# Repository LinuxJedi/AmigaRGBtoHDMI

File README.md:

# AmigaRGBtoHDMI

LinuxJedi's designs for Amiga RGBtoHDMI boards.

**ATTENTION PI Zero 2W users**: You can now use a Pi Zero 2W with the CPLD RGBtoHDMI using the December 24th 2021 release.

## Amiga RGBtoHDMI Tester

If you are a builder of these boards I have designed a tester that safely tests these boards without requiring a Denise or Amiga. This reduces any potential damage and test if you don't have a specific Amiga model. These can be found [on Tindie](https://www.tindie.com/products/linuxjedi/amiga-rgbtohdmi-tester/).

## Choosing a CPLD

I am deliberately vague in which CPLD can be used in the boards here because many variants will work. Given chip shortages in recent years, you might want to pick any chip you can obtain rather than what is normally cheapest. I'll give a breakdown of what the model numbers look like and what to look out for. As an example I'll use `XC9572XL-10VQG44C`:

* `XC9572XL` - This part of the model number is required. Defines the type of logic chip and the number of logic cells. This is what you should search for from your supplier and then use the below to pick the right chip for you.
* `10` - is the maximum speed grade in ns. 10 is the slowest (cheapest) you can buy. The max speed this board will go is 35ns, so 10ns is plenty.
* `VQ` - means it is a QFP. You could modify the board to accept the PLCC variant, but that would require you to make some changes in KiCad. The firmware is compatible with both.
* `G` - means lead-free / RoHS compliant. Without the `G` means the legs have lead.
* `44` - number of pins. You could in-theory modify the board for more pins in KiCad. This would require a firmware change too, which in-turn means modifying the firmware loader, so I don't recommend it.
* `C` - Consumer grade (cheapest), if there is an `I` here that means "Industrial grade" (more expensive) and `A` means "Automotive grade" (crazy expensive). This mostly defines the max/min temperature the chip will work at.

My recommendation if you can obtain it, is the XC9572XL-10VQG44C (or without the `G`). But the only important parts are the `XC9572XL`, the `VQ` and the `44`.

## Projects in This Tree

### Amiga500CPLD

Amiga 500 CPLD variant that does not require a jumper and has no sparkling pixel issues.

### Amiga2000CPLDSlot

Amiga 2000 CPLD variant that does not require a jumper and has no sparkling pixel issues

### Amiga1000CPLD

Amiga 1000 CPLD variant that does not require a jumper and has no sparkling pixel issues

### Legacy boards

The legacy boards directory contains:

* Amiga 2000 RGBtoHDMI v2
* Amiga 2000 CPLD RGBtoHDMI v1.2
* Amiga 2000 CPLD RGBtoHDMI v2.1

These have been superseeded by the Amiga 2000 CPLD RGBtoHDMI v2.2 board.

* Amiga 500 CPLD v1

This has been superseeded by the Amiga 500 CPLD RGBtoHDMI v2.0 board.

## Other versions

- c0pperdragon's - The excellent original c0pperdragon design can be found at: https://github.com/c0pperdragon/Amiga-Digital-Video/
- solarmon's - Improved versions of c0pperdragon's design to relocate the Pi and add additional features:https://github.com/solarmon/RGBtoHDMI

Please add pull requests to link to your variants here.

## Software

The software used for this project can be found at https://github.com/hoglet67/RGBtoHDMI/

## Troubleshooting

### Cannot use the CPLD flash menu

By default the RGBtoHDMI software is in three button mode. You need to copy the profiles in the instructions for your board which sets up a few things including the single button mode.

## Ready Built Boards

If you want a ready built board for either design please contact andrew@linuxjedi.co.uk and I can put you in touch with whoever is building / selling at a reasonable price.

Likewise if you are a someone selling these designs, please let me know if you want me to put you in touch with buyers who contact me.

I also sell some of these designs [on Tindie](https://www.tindie.com/stores/linuxjedi/).

Alternatively I've made the PCBs available on PCBWay here: https://www.pcbway.com/project/member/?bmbno=0369642B-E3DA-48

## Sponsorship

If you like these projects and have built / sold a few yourself, please consider sponsoring. R&D for these projects isn't cheap and the sponsorship money goes into more designs for the future. Links for this are can be found in the "Sponsor" button at the top of the GitHub page for this project.

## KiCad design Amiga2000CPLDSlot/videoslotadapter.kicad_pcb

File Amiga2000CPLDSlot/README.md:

# Amiga CPLD Video Slot Adapter

This adaptor uses a CPLD to pass the RGB and sync signals from the Amiga 2000 video slot to the Rasperry Pi Zero. It derives the pixel clock in a very different way to other designs and therefore does not require a jumper for Denise / Super Denise and has no "sparkling" pixel issues. It also has the advantage of being firmware upgradable if there are any issues found in the logic.

Version 2 of this board is logically identical to version 1, but is designed to be easier to build and easier for the user to install. The Pi faces the rear of the Amiga so that the HDMI can be plugged directly into it and instead of wires it uses physical buttons.

Version 2.2 has been changed to make the board smaller. It includes a fuse due to a few users misaligning the Pi, causing a sort between +5v and GND which in-turn caused the +5v line to burn. It also includes an optional LED to indicate there is power to the +5v line (that the fuse hasn't blown).

**ATTENTION PI Zero 2W users**: You can now use a Pi Zero 2W with the CPLD RGBtoHDMI using 24th December 2021 release onwards.

## BOM

| Symbol       | Component                                    |
| ------------ | -------------------------------------------- |
| C1 - C3      | 0.1uF 0603                                   |
| J1           | 2x20pin socket 2.54mm                        |
| SW1 - SW3    | SKHHLQA010 90° SPST 8.35mm push button       |
| R1           | 1K 0603                                      |
| R3           | 4.7K 0603                                    |
| U1           | XC9572XL 44pin QFP                           |
| F1           | Littlefuse 1206L075THYR                      |
| D1           | Any 0603 LED                                 |
| R2           | A 0603 resistor between the LED and +5v line |

### Notes

- R1 needs to be a 1K pull resistor due to the low value internal I2C pull resisors in the Pi. If the value is too high then the software won't detect this is an Amiga board and won't show the correct firmware in the recovery menu.
- The F1 fuse can be any 1206 fuse with a hold current of 0.75A or greater. You could also just use a 0ohm resistor if you do not wish to use a fuse.
- D1 and R2 are optional, used as indication that the 5V line is being provided to the Pi and there is no fuse trip.
- This board can be used in single button mode with just SW1.
- You can use smaller push buttons but they won't reach outside of the A2000's case, this may be fine with the correct bracket.
- Brackets for the original A2000 RGBtoHDMI boards are **NOT** compatible, the mounting holes have been moved.
- It is recommended you use 4x11mm M2.5 standoffs to hold the Pi in place, alternatively you can use 10mm M2.5 standoffs and 1mm M2.5 washers.
- The board was designed in a KiCad 6.99 nightly build, you will need to use 6.99 (or higher if you are reading this after 7.0 is released) to be able to use the files.

## Pi Software Installation

The software on the Pi should be at least the latest 20211224 release from the [main tree](https://github.com/hoglet67/RGBtoHDMI/releases) or the latest [IanSB beta release](https://github.com/IanSB/RGBtoHDMI/releases) extracted onto a micro SD card in FAT32 format.

You need to copy some canned profile files into place for the board:

* `Amiga_CPLD_Readme/Amiga_2000_CPLD_Setup/profile_6-12_BIT_RGB.txt` to the root of the SD card
* `Amiga_CPLD_Readme/Amiga_2000_CPLD_Setup/Profiles/Default.txt` to the `Profiles` directory

This resolves some issues with mode switching, particularly on NTSC machines.

If you wish to use three button mode, you then need to edit `Profiles/Default.txt` and set the option `single_button_mode=0` (it is near the bottom of the file).

## Flashing the CPLD

The CPLD will need flashing with the `6-12_BIT_RGB_CPLD` firmware. The other firmware options are not compatible with this board.

If you have followed the software steps above you will get a recovery menu, select `6-12_BIT_RGB_CPLD`, confirm and the Pi will flash the CPLD and reboot.

## Initial Setup

You may see a shimmer or wavy effect. This is because the phase is set incorrectly and needs calibration, this is a one-off easy thing to do. If you have a static image such as the Kickstart 1.3 boot screen or Workbench with no mouse movement you can use the "Auto Calibrate Video Settings" option (it will require you to select twice to activate). Alternatively you can go into the "Sampling" menu and change the "Sampling Phase" until the image looks correct. Typically 0, 3 or 5 will work fine, but it could be different in each machine.

Once calibrated choose "Save Configuration" and this will be remembered for subsequent boots.

## Buying PCBs

You can buy PCBs from my store, [Retro Supplies](https://www.retrosupplies.co.uk/amiga-rgbtohdmi/rgbtohdmi-for-amiga-2000-v22-pcb-only).

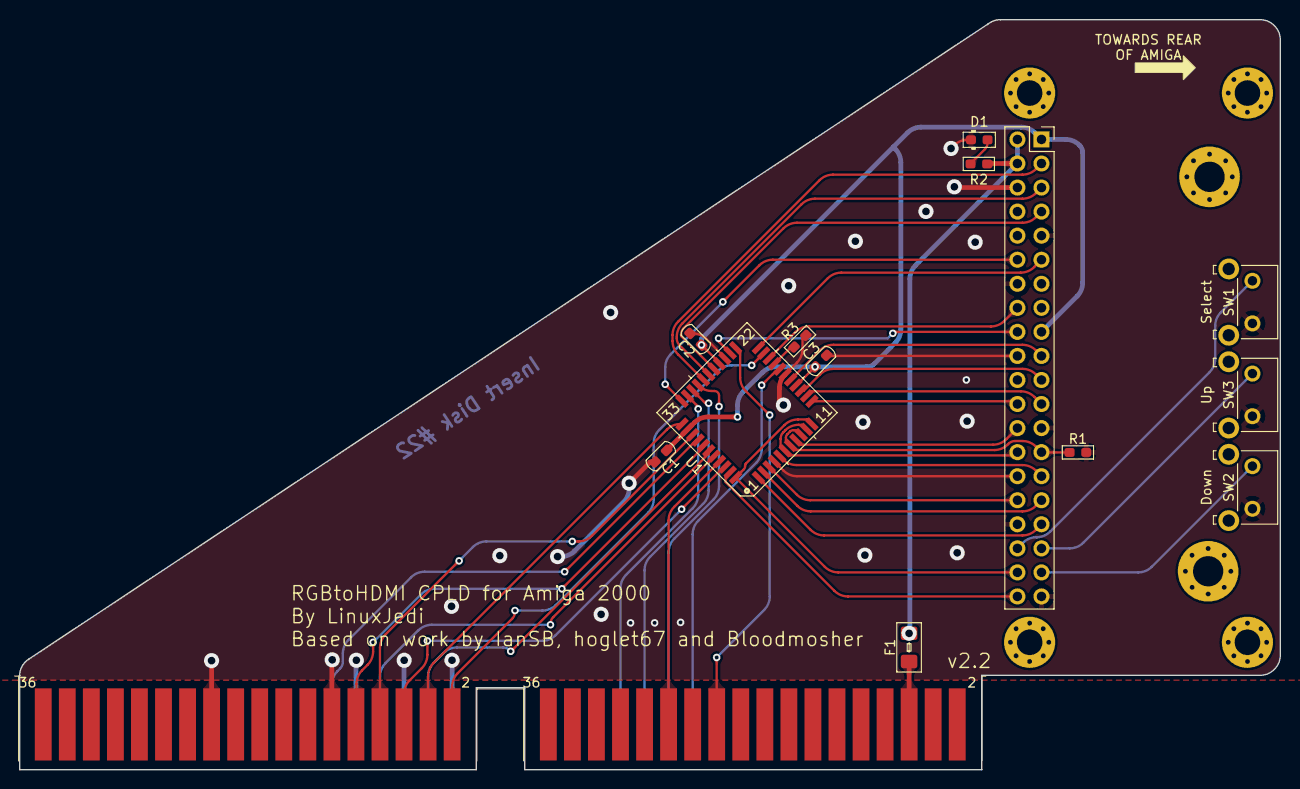
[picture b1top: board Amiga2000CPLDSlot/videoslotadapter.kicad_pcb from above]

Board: 2 copper layers, 133.1 x 79.2 mm, 20 parts (0 on the bottom side), 43 nets.

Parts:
C1, C2, C3: 0.1uF; C_0603_1608Metric_Pad1.08x0.95mm
D1: LED; D_0603_1608Metric_Pad1.05x0.95mm
F1: 500mA; Fuse_1206_3216Metric_Pad1.42x1.75mm_BigPads
H1, H2, H3, H4: MountingHole; MountingHole_2.7mm_M2.5_Pad_Via
H5, H6: MountingHole; MountingHole_3.2mm_M3_Pad_Via
J1: Raspberry_Pi_2_3; PinSocket_2x20_P2.54mm_Vertical
JVideoSlot1: A2000_Video_Slot_Phys; A2000_Video_Slot
R1: 1K; R_0603_1608Metric_Pad1.05x0.95mm_HandSolder
R2: R; R_0603_1608Metric_Pad1.05x0.95mm_HandSolder
R3: 4.7K; R_0603_1608Metric_Pad1.05x0.95mm_HandSolder
SW1: Select; SW_Tactile_SKHH_Angled
SW2: Down; SW_Tactile_SKHH_Angled
SW3: Up; SW_Tactile_SKHH_Angled
U1: XC9572VQ44; TQFP-44_10x10mm_P0.8mm

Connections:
+3V3: C1.1, C2.1, C3.1, J1.1 (3V3), J1.17 (3V3), U1.15 (VCC), U1.26 (VCCIO), U1.35 (VCC)
+5V: F1.2, J1.2 (5V), J1.4 (5V), R2.2
/B0: JVideoSlot1.23 (BO=DI(47-Ohm)), U1.18 (FB3M16)
/B1: JVideoSlot1.46 (B1), U1.38 (FB2M17)
/B2: JVideoSlot1.47 (B2), U1.37 (FB2M15)
/B3: JVideoSlot1.25 (B3=DB(47-Ohm)), U1.30 (FB2M5)
/CLKEN: J1.28 (ID_SC/GPIO1), U1.6 (FB3M5), U1.10 (TMS)
/DETECT: R3.1, U1.19 (FB4M2)
/G0: JVideoSlot1.42 (G0), U1.42 (FB1M8)
/G1: JVideoSlot1.43 (G1), U1.40 (FB1M5)
/G2: JVideoSlot1.44 (G2), U1.36 (I/O/GTS1)
/G3: JVideoSlot1.27 (G3=DG(47-Ohm)), U1.31 (FB2M6)
/GPIO0: J1.27 (ID_SD/GPIO0), R1.1, U1.7 (FB3M8), U1.9 (TDI)
/GPIO2: J1.3 (SDA/GPIO2), U1.29 (FB2M2)
/GPIO3: J1.5 (SCL/GPIO3), U1.28 (FB4M17)
/GPIO4: J1.7 (GCLK0/GPIO4), U1.27 (FB4M15)
/GPIO5: J1.29 (GCLK1/GPIO5), U1.5 (FB3M2)
/GPIO6: J1.31 (GCLK2/GPIO6), U1.2 (FB1M15)
/GPIO7: J1.26 (~CE1/GPIO7), U1.8 (FB3M9)
/GPIO8: J1.24 (~CE0/GPIO8), U1.12 (FB3M11)
/GPIO9: J1.21 (MISO0/GPIO9), U1.14 (FB3M15)
/GPIO10: J1.19 (MOSI0/GPIO10), U1.16 (FB3M17)
/GPIO11: J1.23 (SCLK0/GPIO11), U1.13 (FB3M14)
/GPIO12: J1.32 (PWM0/GPIO12), U1.3 (FB1M17)
/GPIO13: J1.33 (PWM1/GPIO13), U1.1 (I/O/GCK3)
/GPIO16: J1.36 (GPIO16), SW1.1
/GPIO17: J1.11 (GPIO17), U1.22 (FB4M11)
/GPIO18: J1.12 (GPIO18/PWM0), U1.33 (I/O/GSR)
/GPIO19: J1.35 (GPIO19/MISO1), SW3.1
/GPIO20: J1.38 (GPIO20/MOSI1), U1.11 (TCK), U1.44 (I/O/GCK2)
/GPIO21: J1.40 (GPIO21/SCLK1), U1.43 (I/O/GCK1)
/GPIO23: J1.16 (GPIO23), U1.20 (FB4M5)
/GPIO24: J1.18 (GPIO24), U1.24 (TDO)
/GPIO26: J1.37 (GPIO26), SW2.1
/HSYNC: JVideoSlot1.22 (/HSYNC(47-Ohm)), U1.23 (FB4M14)
/R0: JVideoSlot1.38 (R0), U1.21 (FB4M8)
/R1: JVideoSlot1.39 (R1), U1.39 (FB1M2)
/R2: JVideoSlot1.40 (R2), U1.34 (I/O/GTS2)
/R3: JVideoSlot1.29 (R3=DR(47-Ohm)), U1.32 (FB2M8)
/VSYNC: JVideoSlot1.26 (/VSYNC(47-Ohm)), U1.41 (FB1M6)
GND: C1.2, C2.2, C3.2, D1.1 (K), J1.6 (GND), J1.9 (GND), J1.14 (GND), J1.20 (GND), J1.25 (GND), J1.30 (GND), J1.34 (GND), J1.39 (GND), JVideoSlot1.37 (Ground), JVideoSlot1.41 (Ground), JVideoSlot1.45 (Ground), JVideoSlot1.48 (Ground), JVideoSlot1.58 (Ground), R1.2, R3.2, SW1.2, SW2.2, SW3.2, U1.4 (GND), U1.17 (GND), U1.25 (GND)
unnamed: D1.2 (A), R2.1
VCC: F1.1, JVideoSlot1.6 (+5_VDC_(2A))

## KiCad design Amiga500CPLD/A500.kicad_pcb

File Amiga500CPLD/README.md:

# Amiga 500 CPLD RGBtoHDMI

This adaptor uses a CPLD to pass the RGB and sync signals from the Amiga 500 Denise socket to the Rasperry Pi Zero. It derives the pixel clock in a very different way to the c0pperdragon design and therefore does not require a jumper for Denise / Super Denise and has no "sparkling" pixel issues. It also has the advantage of being firmware upgradable if there are any issues found in the logic.

**ATTENTION PI Zero 2W users**: You can now use a Pi Zero 2W with the CPLD RGBtoHDMI using the December 24th 2021 release.

## BOM

| Symbol     | Component                         |
| ---------- | --------------------------------- |
| C1 - C3    | 0.1uF 0603                        |
| J1         | 2x20pin socket 2.54mm             |
| JP1        | 2pin right angle header 2.54mm    |
| J2         | 1pin right angle header 2.54mm    |
| R1         | 1K 0603                           |
| R2         | 4.7K 0603                         |
| U1         | 48pin DIP socket 2.54mm           |
| U2         | 2x24pin SILs machined pins 2.54mm |
| U3         | XC9572XL 44pin QFP                |

### Notes

- It is important that R1 is 1K due to the low value of the internal pull resistor in GPIO0 of the Pi, the other pull resistors are more flexible (R1 is optional as the Pi will pull this internally). If the value is too high then the software won't detect this is an Amiga board and won't show the correct firmware in the recovery menu.
- You'll need some kind of push button to connect to JP1
- J2 is optional, it is only needed for revision 3 motherboards to clip onto pin 9 of U41 on the Amiga (photo coming soon)
- The Pi mounting holes are M2.5, 11mm posts or 10mm with 1mm washers are recommended

## Pi Software Installation

The software on the Pi should be at least the latest 20210529 release from the [main tree](https://github.com/hoglet67/RGBtoHDMI/releases) or the latest [IanSB beta release](https://github.com/IanSB/RGBtoHDMI/releases) extracted onto a micro SD card in FAT32 format.

You need to copy some canned profile files into place for the board:

* `Amiga_CPLD_Readme/Amiga_CPLD_Setup/profile_6-12_BIT_RGB.txt` to the root of the SD card
* `Amiga_CPLD_Readme/Amiga_CPLD_Setup/Profiles/Default.txt` to the `Profiles` directory

This resolves some issues with mode switching, particularly on NTSC machines. The profile copied will automatically set `single_button_mode`.

## Flashing the CPLD

The CPLD will need flashing with the `6-12_BIT_RGB_CPLD` firmware. The other firmware options are not compatible with the profiles.

If you have followed the software steps above you will get a recovery menu, select `6-12_BIT_RGB_CPLD`, confirm and the Pi will flash the CPLD and reboot. You can then jump to the Initial Setup section below.

## Initial Setup

You may also a shimmer or wavy effect. This is because the phase is set incorrectly and needs calibration, this is a one-off easy thing to do. If you have a static image such as the Kickstart 1.3 boot screen or Workbench with no mouse movement you can use the "Auto Calibrate Video Settings" option (it will require you to select twice to activate). Alternatively you can go into the "Sampling" menu and change the "Sampling Phase" until the image looks correct. Typically 0, 3 or 5 will work fine, but it could be different in each machine.

Once calibrated choose "Save Configuration" and this will be remembered for subsequent boots.

## Buying PCBs

I've made the [PCBs available on PCBWay](https://www.pcbway.com/project/shareproject/Amiga_500_CPLD_RGBtoHDMI_v2_fb52eff9.html).

You can also purchase PCBs from me [via Tindie](https://www.tindie.com/products/linuxjedi/amiga-500-rgb-to-hdmi-pcb/).

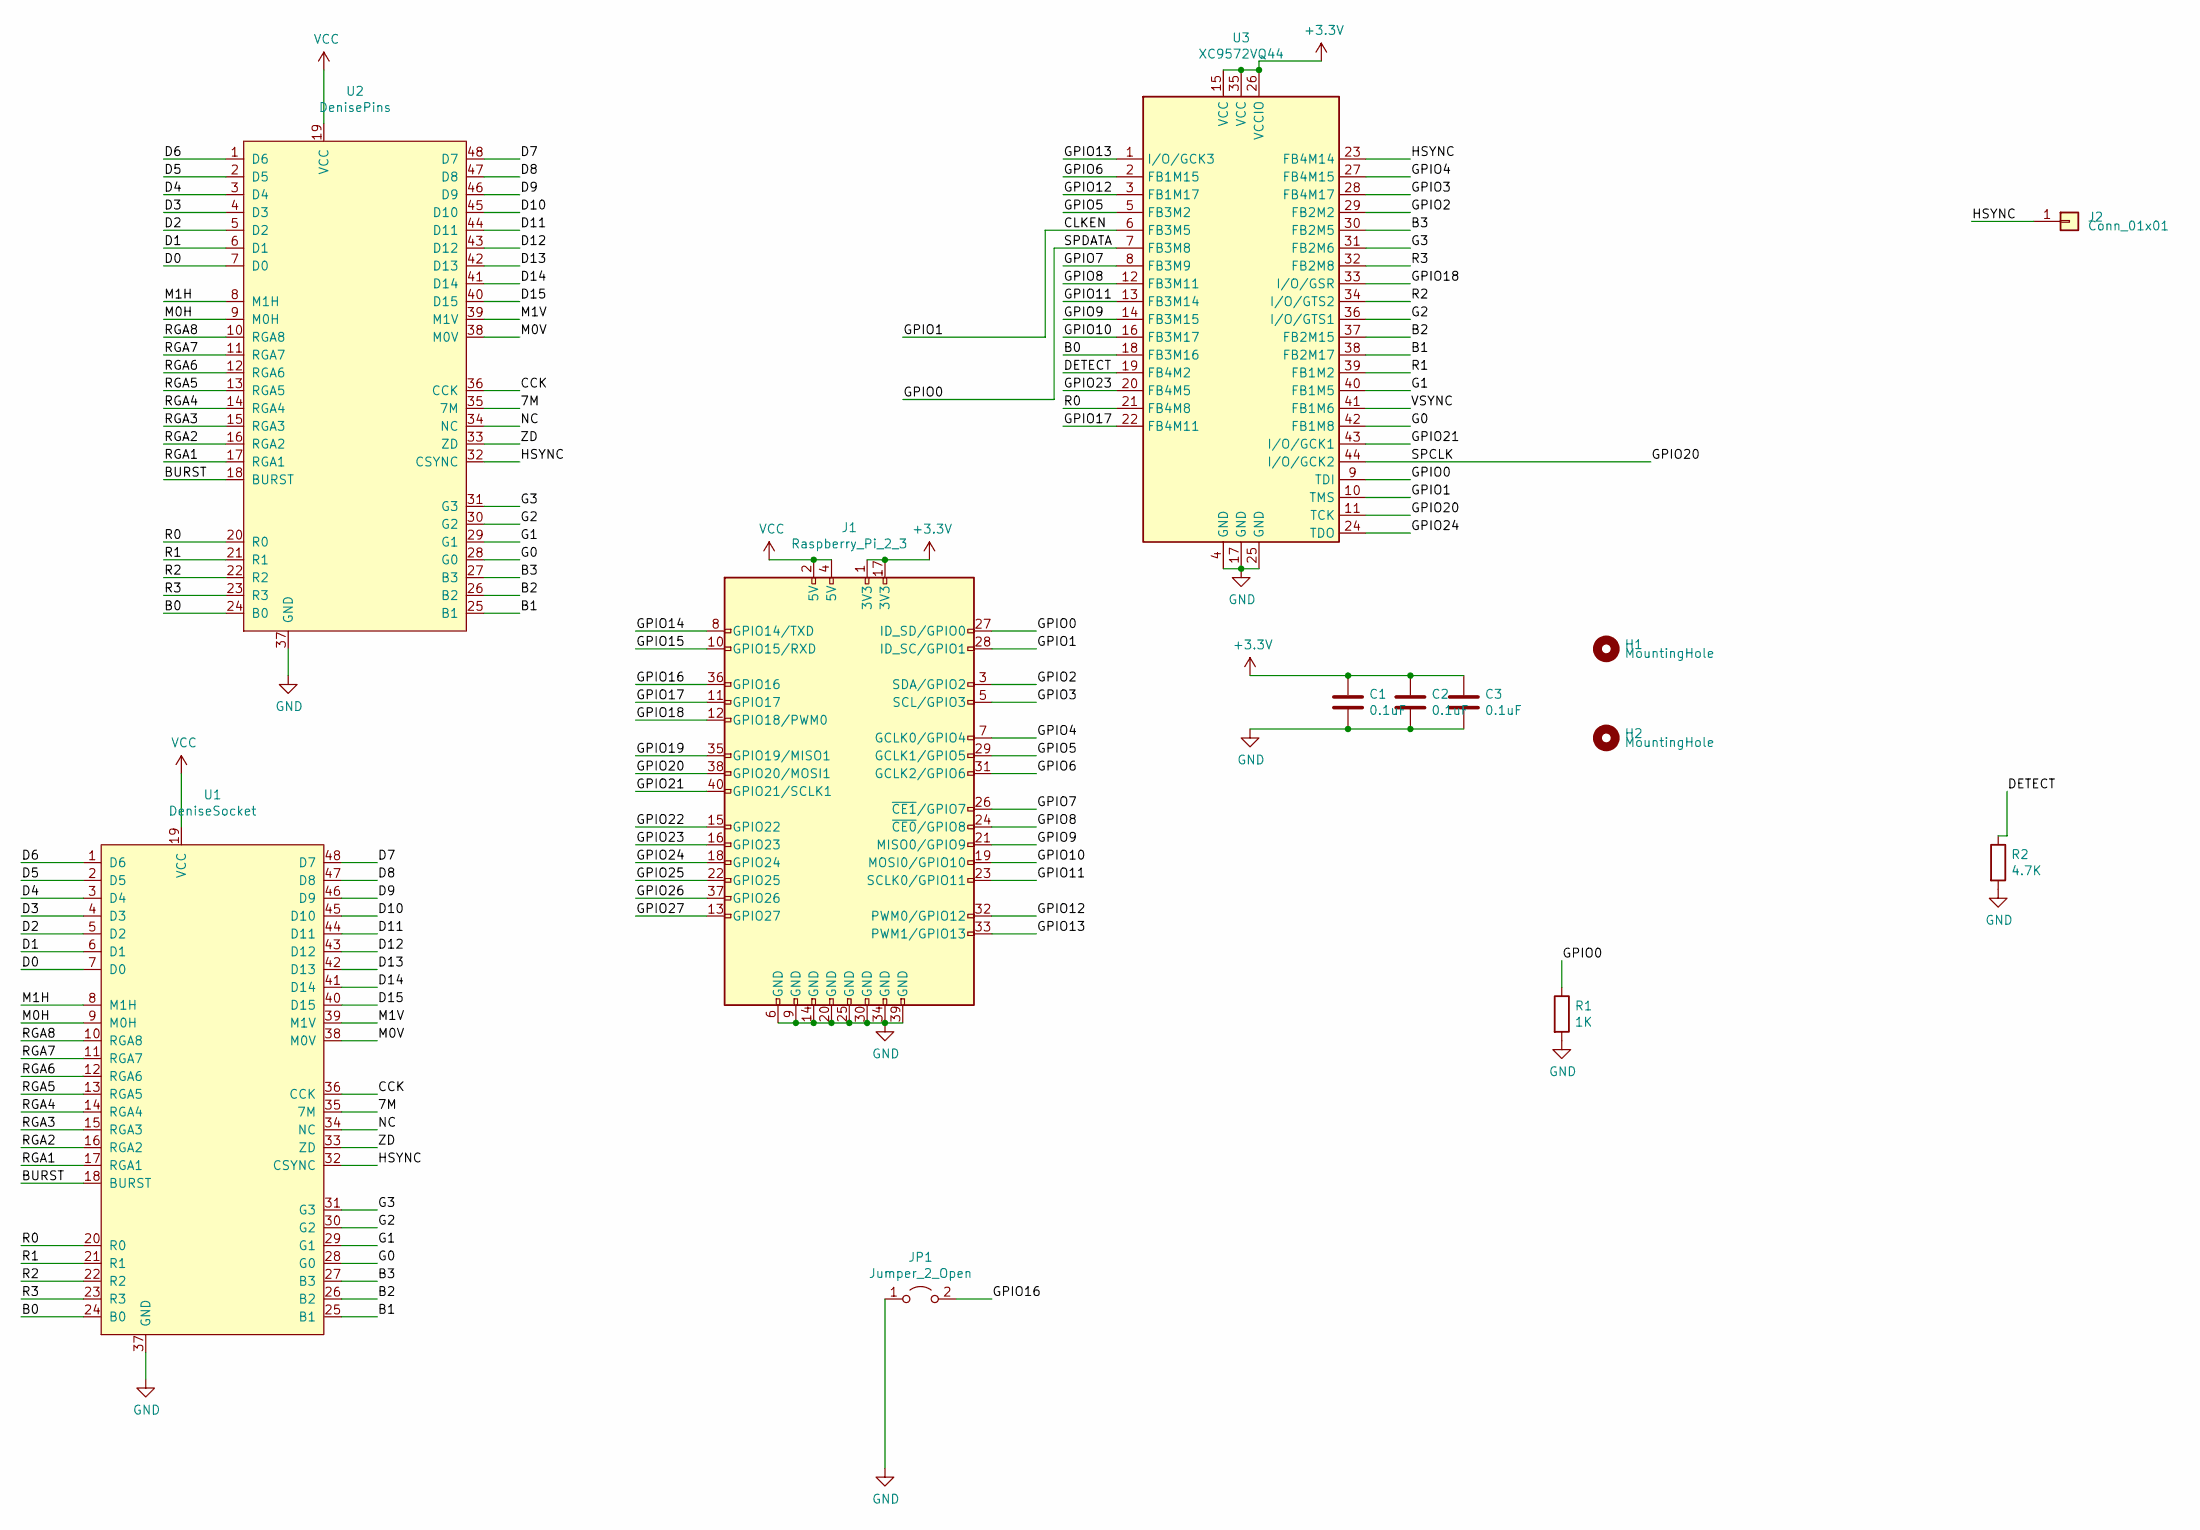
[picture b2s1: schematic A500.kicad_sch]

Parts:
C1, C2, C3: 0.1uF; C_0603_1608Metric_Pad1.08x0.95mm
H1, H2: MountingHole; MountingHole_2.5mm_Pad
J1: Raspberry_Pi_2_3; PinSocket_2x20_P2.54mm_Vertical
J2: Conn_01x01; PinHeader_1x01_P2.54mm_Horizontal
JP1: Jumper_2_Open; PinHeader_1x02_P2.54mm_Horizontal
R1: 1K; R_0603_1608Metric_Pad1.05x0.95mm
R2: 4.7K; R_0603_1608Metric_Pad1.05x0.95mm
U1: DeniseSocket; DIP-48_W15.24mm_Socket_LongPads
U2: DenisePins; DIP-48_W15.24mm_LongPads
U3: XC9572VQ44; TQFP-44_10x10mm_P0.8mm

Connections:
+3V3: C1.1, C2.1, C3.1, J1.1 (3V3), J1.17 (3V3), U3.15 (VCC), U3.26 (VCCIO), U3.35 (VCC)
/7M: U1.35 (7M), U2.35 (7M)
/B0: U1.24 (B0), U2.24 (B0), U3.18 (FB3M16)
/B1: U1.25 (B1), U2.25 (B1), U3.38 (FB2M17)
/B2: U1.26 (B2), U2.26 (B2), U3.37 (FB2M15)
/B3: U1.27 (B3), U2.27 (B3), U3.30 (FB2M5)
/BURST: U1.18 (BURST), U2.18 (BURST)
/CCK: U1.36 (CCK), U2.36 (CCK)
/CLKEN: J1.28 (ID_SC/GPIO1), U3.6 (FB3M5), U3.10 (TMS)
/D0: U1.7 (D0), U2.7 (D0)
/D1: U1.6 (D1), U2.6 (D1)
/D2: U1.5 (D2), U2.5 (D2)
/D3: U1.4 (D3), U2.4 (D3)
/D4: U1.3 (D4), U2.3 (D4)
/D5: U1.2 (D5), U2.2 (D5)
/D6: U1.1 (D6), U2.1 (D6)
/D7: U1.48 (D7), U2.48 (D7)
/D8: U1.47 (D8), U2.47 (D8)
/D9: U1.46 (D9), U2.46 (D9)
/D10: U1.45 (D10), U2.45 (D10)
/D11: U1.44 (D11), U2.44 (D11)
/D12: U1.43 (D12), U2.43 (D12)
/D13: U1.42 (D13), U2.42 (D13)
/D14: U1.41 (D14), U2.41 (D14)
/D15: U1.40 (D15), U2.40 (D15)
/DETECT: R2.1, U3.19 (FB4M2)
/G0: U1.28 (G0), U2.28 (G0), U3.42 (FB1M8)
/G1: U1.29 (G1), U2.29 (G1), U3.40 (FB1M5)
/G2: U1.30 (G2), U2.30 (G2), U3.36 (I/O/GTS1)
/G3: U1.31 (G3), U2.31 (G3), U3.31 (FB2M6)
/GPIO0: J1.27 (ID_SD/GPIO0), R1.1, U3.7 (FB3M8), U3.9 (TDI)
/GPIO2: J1.3 (SDA/GPIO2), U3.29 (FB2M2)
/GPIO3: J1.5 (SCL/GPIO3), U3.28 (FB4M17)
/GPIO4: J1.7 (GCLK0/GPIO4), U3.27 (FB4M15)
/GPIO5: J1.29 (GCLK1/GPIO5), U3.5 (FB3M2)
/GPIO6: J1.31 (GCLK2/GPIO6), U3.2 (FB1M15)
/GPIO7: J1.26 (~CE1/GPIO7), U3.8 (FB3M9)
/GPIO8: J1.24 (~CE0/GPIO8), U3.12 (FB3M11)
/GPIO9: J1.21 (MISO0/GPIO9), U3.14 (FB3M15)
/GPIO10: J1.19 (MOSI0/GPIO10), U3.16 (FB3M17)
/GPIO11: J1.23 (SCLK0/GPIO11), U3.13 (FB3M14)
/GPIO12: J1.32 (PWM0/GPIO12), U3.3 (FB1M17)
/GPIO13: J1.33 (PWM1/GPIO13), U3.1 (I/O/GCK3)
/GPIO14: J1.8 (GPIO14/TXD)
/GPIO15: J1.10 (GPIO15/RXD)
/GPIO16: J1.36 (GPIO16), JP1.2 (B)
/GPIO17: J1.11 (GPIO17), U3.22 (FB4M11)
/GPIO18: J1.12 (GPIO18/PWM0), U3.33 (I/O/GSR)
/GPIO19: J1.35 (GPIO19/MISO1)
/GPIO20: J1.38 (GPIO20/MOSI1), U3.11 (TCK), U3.44 (I/O/GCK2)
/GPIO21: J1.40 (GPIO21/SCLK1), U3.43 (I/O/GCK1)
/GPIO22: J1.15 (GPIO22)
/GPIO23: J1.16 (GPIO23), U3.20 (FB4M5)
/GPIO24: J1.18 (GPIO24), U3.24 (TDO)
/GPIO25: J1.22 (GPIO25)
/GPIO26: J1.37 (GPIO26)
/GPIO27: J1.13 (GPIO27)
/HSYNC: J2.1, U1.32 (CSYNC), U2.32 (CSYNC), U3.23 (FB4M14)
/M0H: U1.9 (M0H), U2.9 (M0H)
/M0V: U1.38 (M0V), U2.38 (M0V)
/M1H: U1.8 (M1H), U2.8 (M1H)
/M1V: U1.39 (M1V), U2.39 (M1V)
/NC: U1.34 (NC), U2.34 (NC)
/R0: U1.20 (R0), U2.20 (R0), U3.21 (FB4M8)
/R1: U1.21 (R1), U2.21 (R1), U3.39 (FB1M2)
/R2: U1.22 (R2), U2.22 (R2), U3.34 (I/O/GTS2)
/R3: U1.23 (R3), U2.23 (R3), U3.32 (FB2M8)
/RGA1: U1.17 (RGA1), U2.17 (RGA1)
/RGA2: U1.16 (RGA2), U2.16 (RGA2)
/RGA3: U1.15 (RGA3), U2.15 (RGA3)
/RGA4: U1.14 (RGA4), U2.14 (RGA4)
/RGA5: U1.13 (RGA5), U2.13 (RGA5)
/RGA6: U1.12 (RGA6), U2.12 (RGA6)
/RGA7: U1.11 (RGA7), U2.11 (RGA7)
/RGA8: U1.10 (RGA8), U2.10 (RGA8)
/VSYNC: U3.41 (FB1M6)
/ZD: U1.33 (ZD), U2.33 (ZD)
GND: C1.2, C2.2, C3.2, J1.6 (GND), J1.9 (GND), J1.14 (GND), J1.20 (GND), J1.25 (GND), J1.30 (GND), J1.34 (GND), J1.39 (GND), JP1.1 (A), R1.2, R2.2, U1.37 (GND), U2.37 (GND), U3.4 (GND), U3.17 (GND), U3.25 (GND)
VCC: J1.2 (5V), J1.4 (5V), U1.19 (VCC), U2.19 (VCC)

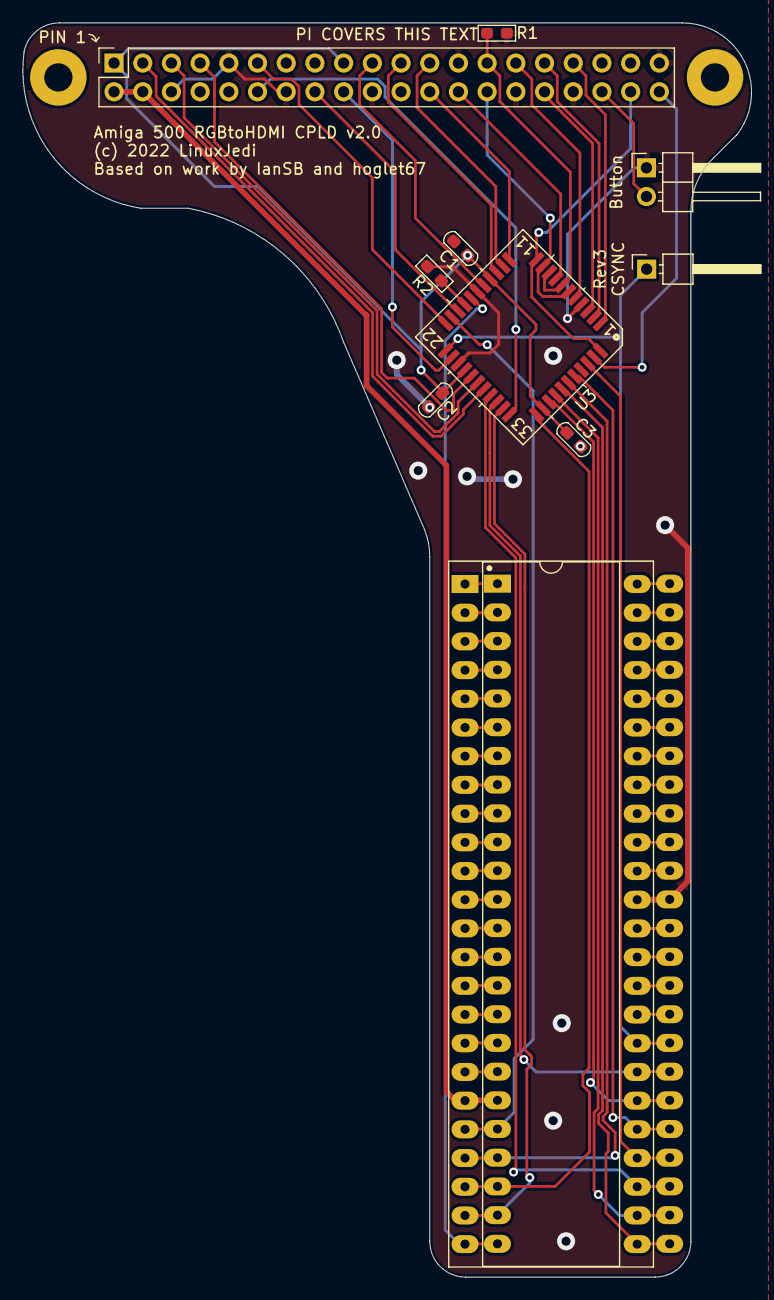
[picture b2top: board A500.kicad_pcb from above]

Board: 2 copper layers, 64.5 x 111.0 mm, 13 parts (0 on the bottom side), 71 nets.

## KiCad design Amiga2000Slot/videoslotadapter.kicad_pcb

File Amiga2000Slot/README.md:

# Amiga Video Slot Adapter V2

This adapter builds on the ideas from the Amiga Denise adapter V2, adapted for use in big box Amiga video slots. LinuxJedi's Version 2 is based on Bloodmosher's V1 design but has been modified for reliability and to provide timing options.

The main differences from the Amiga Denise V2 are:
- The 7MHZ signal is derived via C1 XNOR C3 since 7MHZ is not available directly from the video slot
- Two button connectors allow for both a rear slot cover bracket button and another to be used, mounted wherever desired

The main differences from the V1 slot adaptor are:
- ICs moved to more appropriate locations
- Fixed floating inputs on U5
- Added ground pour and more grounding points for RGB and Pi
- Manually rerouted everything (fewer signal vias)
- Added option to use U1 for the inverted C1, C3 XNOR (which makes it an XOR)
- Added RC based delay option
- Input capacitor added to the regulator
- Rounded the corners a little more

## LinuxJedi's build notes

### Options

 - For U1 to handle Super Denise timing add 0ohm between pin 1 and 2 of JP2
 - For U5 to handle Super Denies timing add 0ohm between pin 2 and 3 of JP2
 - C6 is an optional capacitor for timing delay, 47pF has been recommended by some but can be left unpopulated
 - R2 is a resistor for timing delay, it needs to be populated, only 0ohm has been tested

### Recommended build

This is what has worked for me, YMMV.

 - Leave U5 and C7 unpopulated
 - 0ohm 0603 (or wire/solder short) between pins 1 and 2 of JP2
 - 0ohm 0603 in R2
 - C6 unpopulated or 47pF 0603
 - Use TI 74LVC ICs (Toshiba 74VHC for U1 has also been tested with this design and appear to work)
 - Use a regulator that is rated for 300mA or higher (I use NCP161 regulators in my builds)

### Recommended ordering

If you are ordering from JLCPCB I recommend the following:

 - Surface Finish: ENIG
 - Gold Fingers: Yes
 - 45° finger chamfered: yes

## Installation notes

- Set the Denise jumper according to which Denise is in your Amiga (Super Denise for 8373, Denise for 8362)
- Orient the PCB such that the end with bracket mounting holes faces the rear of the machine

## Sparkles in the image

There are a few things to try. First if the sparkling is extreme, try swapping the Denise/Super Denise jumper to the opposite setting, this changes the clock used for the RGB timing. Then you can try a 47pF capacitor in C6 and using 74VHC ICs instead of 74LVC.

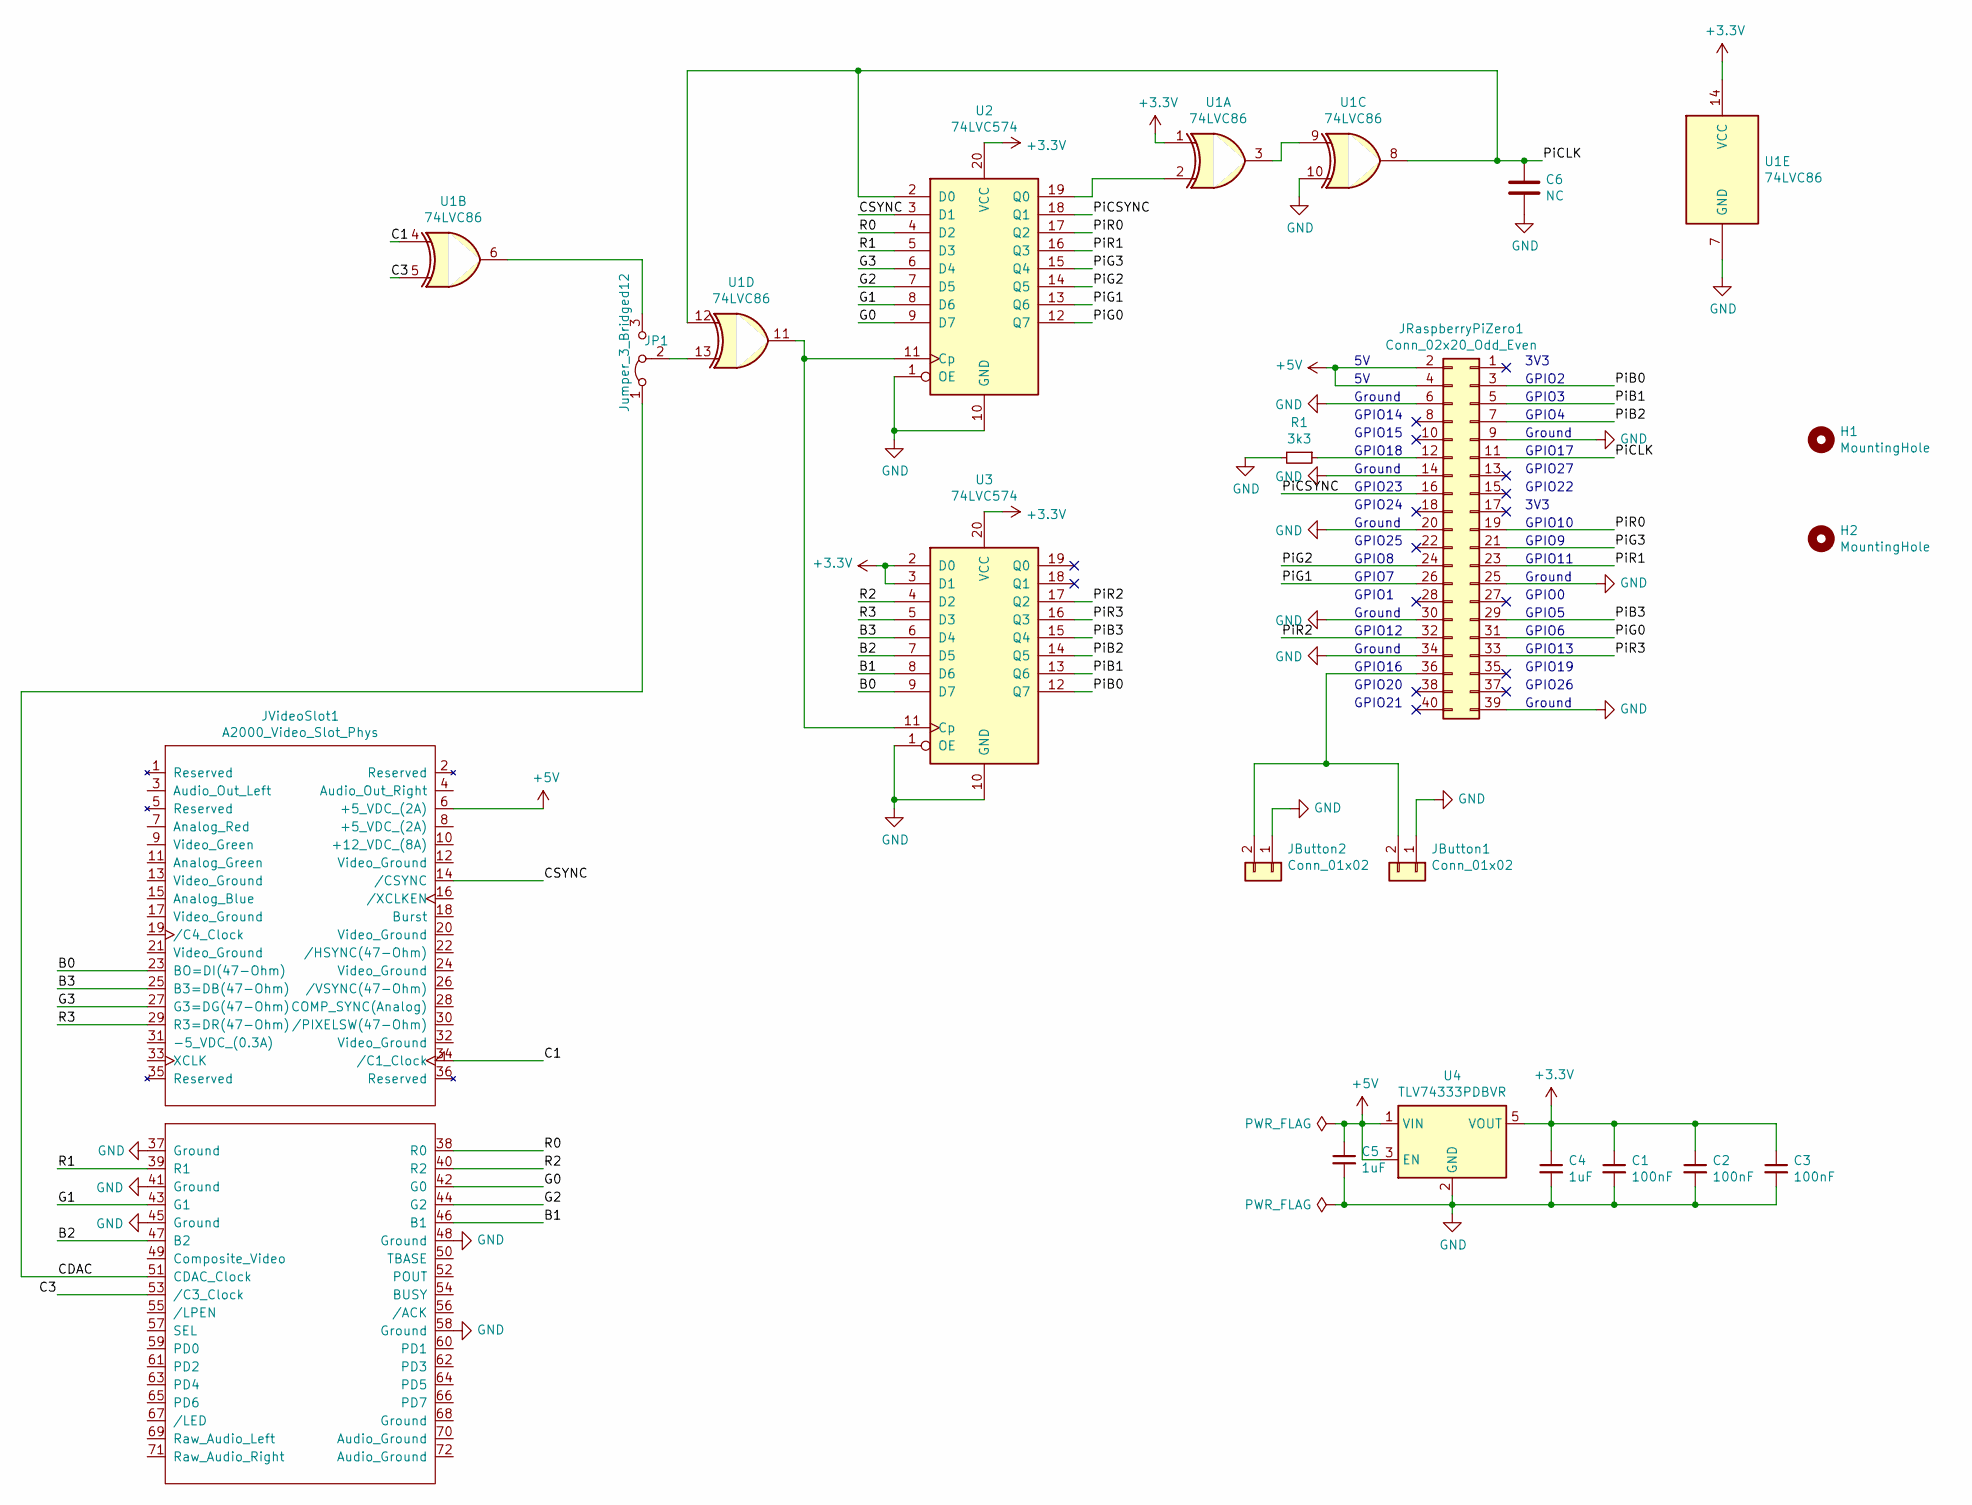
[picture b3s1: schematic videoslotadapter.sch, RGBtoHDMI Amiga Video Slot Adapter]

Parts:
C1, C2, C3: 100nF; C_0603_1608Metric_Pad1.08x0.95mm_HandSolder
C4, C5: 1uF; C_0805_2012Metric_Pad1.18x1.45mm_HandSolder
C6: NC; C_0603_1608Metric_Pad1.08x0.95mm_HandSolder
H1, H2: MountingHole; MountingHole_3.2mm_M3_ISO14580
JButton1, JButton2: Conn_01x02; PinHeader_1x02_P2.54mm_Horizontal
JP1: Jumper_3_Bridged12; PinHeader_1x03_P2.54mm_Horizontal
JRaspberryPiZero1: Conn_02x20_Odd_Even; PinSocket_2x20_P2.54mm_Vertical
JVideoSlot1: A2000_Video_Slot_Phys; A2000_Video_Slot
R1: 3k3; R_0805_2012Metric_Pad1.20x1.40mm_HandSolder
U1: 74LVC86; TSSOP-14_4.4x5mm_P0.65mm
U2, U3: 74LVC574; TSSOP-20_4.4x6.5mm_P0.65mm
U4: TLV74333PDBVR; SOT-23-5_HandSoldering

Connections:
+3V3: C1.1, C2.1, C3.1, C4.1, U1.1, U1.14 (VCC), U2.20 (VCC), U3.2 (D0), U3.3 (D1), U3.20 (VCC), U4.5 (VOUT)
+5V: C5.1, JRaspberryPiZero1.2, JRaspberryPiZero1.4, JVideoSlot1.6 (+5_VDC_(2A)), U4.1 (VIN), U4.3 (EN)
/B0: JVideoSlot1.23 (BO=DI(47-Ohm)), U3.9 (D7)
/B1: JVideoSlot1.46 (B1), U3.8 (D6)
/B2: JVideoSlot1.47 (B2), U3.7 (D5)
/B3: JVideoSlot1.25 (B3=DB(47-Ohm)), U3.6 (D4)
/C1: JVideoSlot1.34 (/C1_Clock), U1.4
/C3: JVideoSlot1.53 (/C3_Clock), U1.5
/CDAC: JP1.1 (A), JVideoSlot1.51 (CDAC_Clock)
/CSYNC: JVideoSlot1.14 (/CSYNC), U2.3 (D1)
/G0: JVideoSlot1.42 (G0), U2.9 (D7)
/G1: JVideoSlot1.43 (G1), U2.8 (D6)
/G2: JVideoSlot1.44 (G2), U2.7 (D5)
/G3: JVideoSlot1.27 (G3=DG(47-Ohm)), U2.6 (D4)
/PiB0: JRaspberryPiZero1.3, U3.12 (Q7)
/PiB1: JRaspberryPiZero1.5, U3.13 (Q6)
/PiB2: JRaspberryPiZero1.7, U3.14 (Q5)
/PiB3: JRaspberryPiZero1.29, U3.15 (Q4)
/PiCLK: C6.1, JRaspberryPiZero1.11, U1.8, U1.12, U2.2 (D0)
/PiCSYNC: JRaspberryPiZero1.16, U2.18 (Q1)
/PiG0: JRaspberryPiZero1.31, U2.12 (Q7)
/PiG1: JRaspberryPiZero1.26, U2.13 (Q6)
/PiG2: JRaspberryPiZero1.24, U2.14 (Q5)
/PiG3: JRaspberryPiZero1.21, U2.15 (Q4)
/PiR0: JRaspberryPiZero1.19, U2.17 (Q2)
/PiR1: JRaspberryPiZero1.23, U2.16 (Q3)
/PiR2: JRaspberryPiZero1.32, U3.17 (Q2)
/PiR3: JRaspberryPiZero1.33, U3.16 (Q3)
/R0: JVideoSlot1.38 (R0), U2.4 (D2)
/R1: JVideoSlot1.39 (R1), U2.5 (D3)
/R2: JVideoSlot1.40 (R2), U3.4 (D2)
/R3: JVideoSlot1.29 (R3=DR(47-Ohm)), U3.5 (D3)
GND: C1.2, C2.2, C3.2, C4.2, C5.2, C6.2, JButton1.1, JButton2.1, JRaspberryPiZero1.6, JRaspberryPiZero1.9, JRaspberryPiZero1.14, JRaspberryPiZero1.20, JRaspberryPiZero1.25, JRaspberryPiZero1.30, JRaspberryPiZero1.34, JRaspberryPiZero1.39, JVideoSlot1.37 (Ground), JVideoSlot1.41 (Ground), JVideoSlot1.45 (Ground), JVideoSlot1.48 (Ground), JVideoSlot1.58 (Ground), R1.2, U1.7 (GND), U1.10, U2.1 (OE), U2.10 (GND), U3.1 (OE), U3.10 (GND), U4.2 (GND)
unnamed: JButton1.2, JButton2.2, JRaspberryPiZero1.36
unnamed: JP1.2 (C), U1.13
unnamed: JP1.3 (B), U1.6
unnamed: JRaspberryPiZero1.12, R1.1
unnamed: U1.2, U2.19 (Q0)
unnamed: U1.3, U1.9
unnamed: U1.11, U2.11 (Cp), U3.11 (Cp)

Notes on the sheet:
3V3
Ground
GPIO14
GPIO15
GPIO18
GPIO23
GPIO24
GPIO25
GPIO8
GPIO7
GPIO1
GPIO12
GPIO16
GPIO21
GPIO20
GPIO2
GPIO3
GPIO4
GPIO17
GPIO27
GPIO22
GPIO10
GPIO9
GPIO11
GPIO0
GPIO5
GPIO6
GPIO13
GPIO19
GPIO26

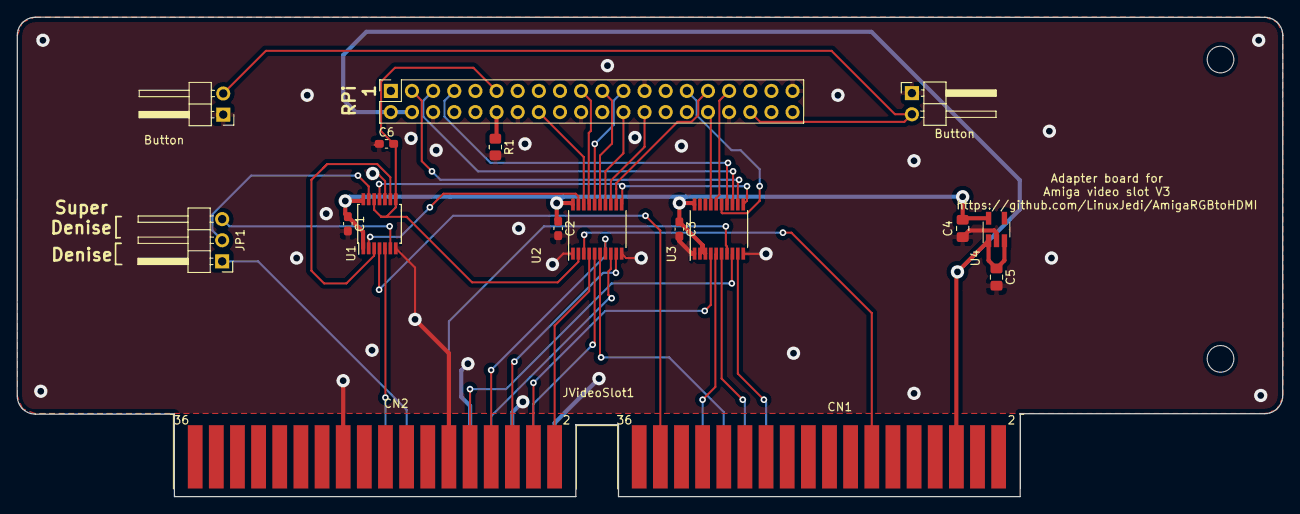
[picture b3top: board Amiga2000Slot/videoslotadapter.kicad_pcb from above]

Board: 2 copper layers, 152.0 x 57.6 mm, 18 parts (0 on the bottom side), 40 nets.

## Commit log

2021-03-28 Initial push of the Amiga 2000 slot version
2021-03-28 Add image to README
2021-03-28 Fix typo in README
2021-04-02 Add notes for JLCPCB ordering
    I've been asked a few times so added to README.
2021-04-02 A2000SlotV3 initial dump
    * Strip out most of the options since we have a pretty stable build now.
    * Add the mounting holes to the schematic and use M3s (need to check
    positioning later)
    Note: At this stage this has not been built and there may be dragons.
2021-04-09 Amiga 500 CPLD variant v1
    This adds the Amiga 500 CPLD variant which does not require a Denise
    jumper and does not have the "sparkling" pixels of other variants.
2021-04-09 Add schematic for Amiga 500 CPLD
2021-04-09 Add info about buying / selling
2021-04-09 Fix CPLD model code
2021-04-10 Add sponsorship message to README
2021-04-11 Add Amiga 2000 CPLD Slot design
    As yet untested
2021-04-12 Add link to solarmon in README
2021-04-12 Amiga2000CPLDSlot v1.1
    Made the following changes after some Discord chats:
    * Added optional buttons 2 & 3
    * Added an arrow to point to the rear of the Amiga
2021-04-15 Make things clearer
    * After feedback on the GPIO JTAG programming section I've made this
    clearer
    * Added silk to the A2000 CPLD slot to mark the wrong way around
2021-04-15 Add GPIO example image
    Thanks to @solarmon for generating and supplying the image
2021-04-17 Add Amiga 1000 CPLD design
    Needs to be a different orientation to the Amiga 500 design. Currently
    untested.
2021-04-22 Update README.md
    Removed future versions section
2021-04-26 Update A500CPLD README with beta software details
    The beta software fixes the single button mode CPLD recovery menu bug
    for us.
2021-05-03 Add Amiga 2000 profiles
2021-05-05 Final tested release of Amiga 2000 CPLD edition
2021-05-10 Update Amiga 1000 and READMEs
    Changes to Amiga 1000 based on feedback:
    * Added a CSYNC hook pin
    * Added optional buttons 2 & 3
    Also moved the buttons to the side as there is more space there.
    A2000 README updated as Beta20 software includes the profiles.
2021-05-27 Fix READMEs
    Whole bunch of changes to READMEs including:
    * PCBWay links
    * New text around Beta29
    * New text around GPIO 0 pull resistor
    * Fixes to errors in the A1000 README
2021-05-28 Add bracket STL link for A2000 CPLD
2021-05-28 Remove profiles now integrated in software tree
2021-05-31 Update software information for new release
    Beta has now been merged into main, so update accordingly.
2021-06-03 Fix text error for A1000 boards
    The "IF YOU CAN READ THIS" text is on the wrong side.
2021-06-07 Fix A500 Gerber format to be PCBWay compatible
2021-06-07 Also fix A1000 Gerbers for PCBWay
2021-08-11 Fix A1000 BOM labelling
2021-08-16 NTSC wiring is the same as PAL for CSYNC
    Confirmed by several sources that the PAL and NTSC CSYNC comes from the
    same place, so alter the README appropriately.
2021-09-10 Update A1000 RGBtoHDMI to rev 1.3
    All SMD components are top side now. Rotated CPLD 90° for better trace
    routing.
2021-09-10 Add LinuxJedi logo footprints
2021-09-10 Fix logo footprint issue...
2021-09-12 Update main README to point to hoglet67 codebase
    Everything required from the IanSB betas was merged long ago.
2021-10-06 Remove LinuxJedi logo from A1000 board
    Fixes #9
2021-11-25 Add note about Pi Zero 2W support
2022-01-09 Add Amiga 2000 CPLD v2.1
    Adds the Amiga 2000 CPLD v2.1 and moves older boards to legacy.
2022-01-23 Several updates to READMEs
2022-01-26 Add Amiga 500 CPLD v2
2022-01-26 Add A500v2 PCBWay link
2022-01-26 Readme update
2022-01-26 Add Tindie link
2022-04-09 Add note about Rejouvenator
    Thanks to Jeff Robertson for testing this.
2022-11-27 Add Amiga 2000 RGBtoHDMI v2.2
2022-11-27 Update READMEs
2023-08-11 Update README with CPLD choices
2023-08-11 Update other READMEs

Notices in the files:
Amiga500CPLD/A500.kicad_pcb:
(c) 2022 LinuxJedi
